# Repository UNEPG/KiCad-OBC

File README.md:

# KiCad-OBC
UNEPG Course Module 4 Lecture 2: PCB Design with KiCad Course Materials.

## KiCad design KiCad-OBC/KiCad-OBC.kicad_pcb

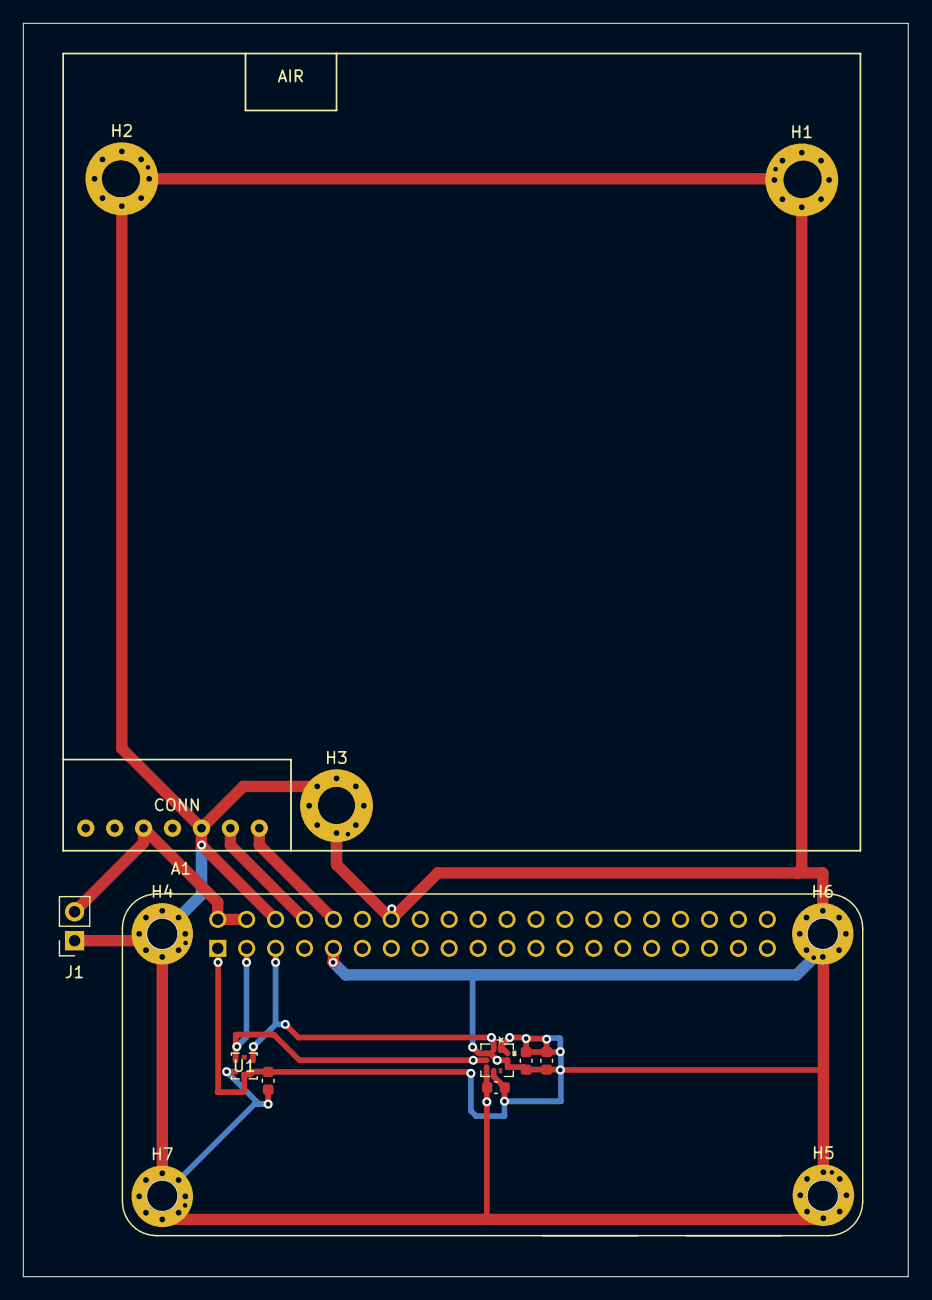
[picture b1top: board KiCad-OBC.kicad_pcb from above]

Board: 2 copper layers, 77.7 x 110.0 mm, 16 parts (0 on the bottom side), 7 nets.

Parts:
A1: ADA3708; RPI-ZERO
C1, C2, C3: 100n; C_0603_1608Metric
C4: 10n; C_0603_1608Metric
H1, H2, H3: 3.2; MountingHole_3.2mm_M3_Pad_Via
H4, H5, H6, H7: 2.75; MountingHole_2.7mm_M2.5_Pad_Via
J1: PWR; PinSocket_1x02_P2.54mm_Vertical
U1: HTS221TR
U2: LPS25H
U3: SDS011

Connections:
+3V3: A1.1 (3V3[1]), C1.1, C2.1, C3.1, C4.1, U1.1 (VDD), U1.6 (CS), U2.1 (VDD_IO), U2.6 (CS), U2.10 (VDD)
+5V: A1.2 (5V[1]), A1.4 (5V[2]), J1.2, U3.3 (5V)
GND: A1.6 (GND[8]), A1.9 (GND[1]), A1.14 (GND[4]), C1.2, C2.2, C3.2, C4.2, H1.1, H2.1, H3.1, H4.1, H5.1, H6.1, H7.1, J1.1, U1.5 (GND), U2.3 (RESERVED), U2.5 (SDO/SA0), U2.8 (GND), U2.9 (GND), U3.5 (GND)
RXPi: A1.10 (RXD0/GPIO15), U3.7 (TX)
SCL: A1.5 (GPIO3/SCL), U1.2 (SCL/SPC), U2.2 (SCL/SPC)
SDA: A1.3 (GPIO2/SDA), U1.4 (SDA/SDI/SDO), U2.4 (SDA/SDI/SDO)
TXPi: A1.8 (TXD0/GPIO14), U3.6 (RX)

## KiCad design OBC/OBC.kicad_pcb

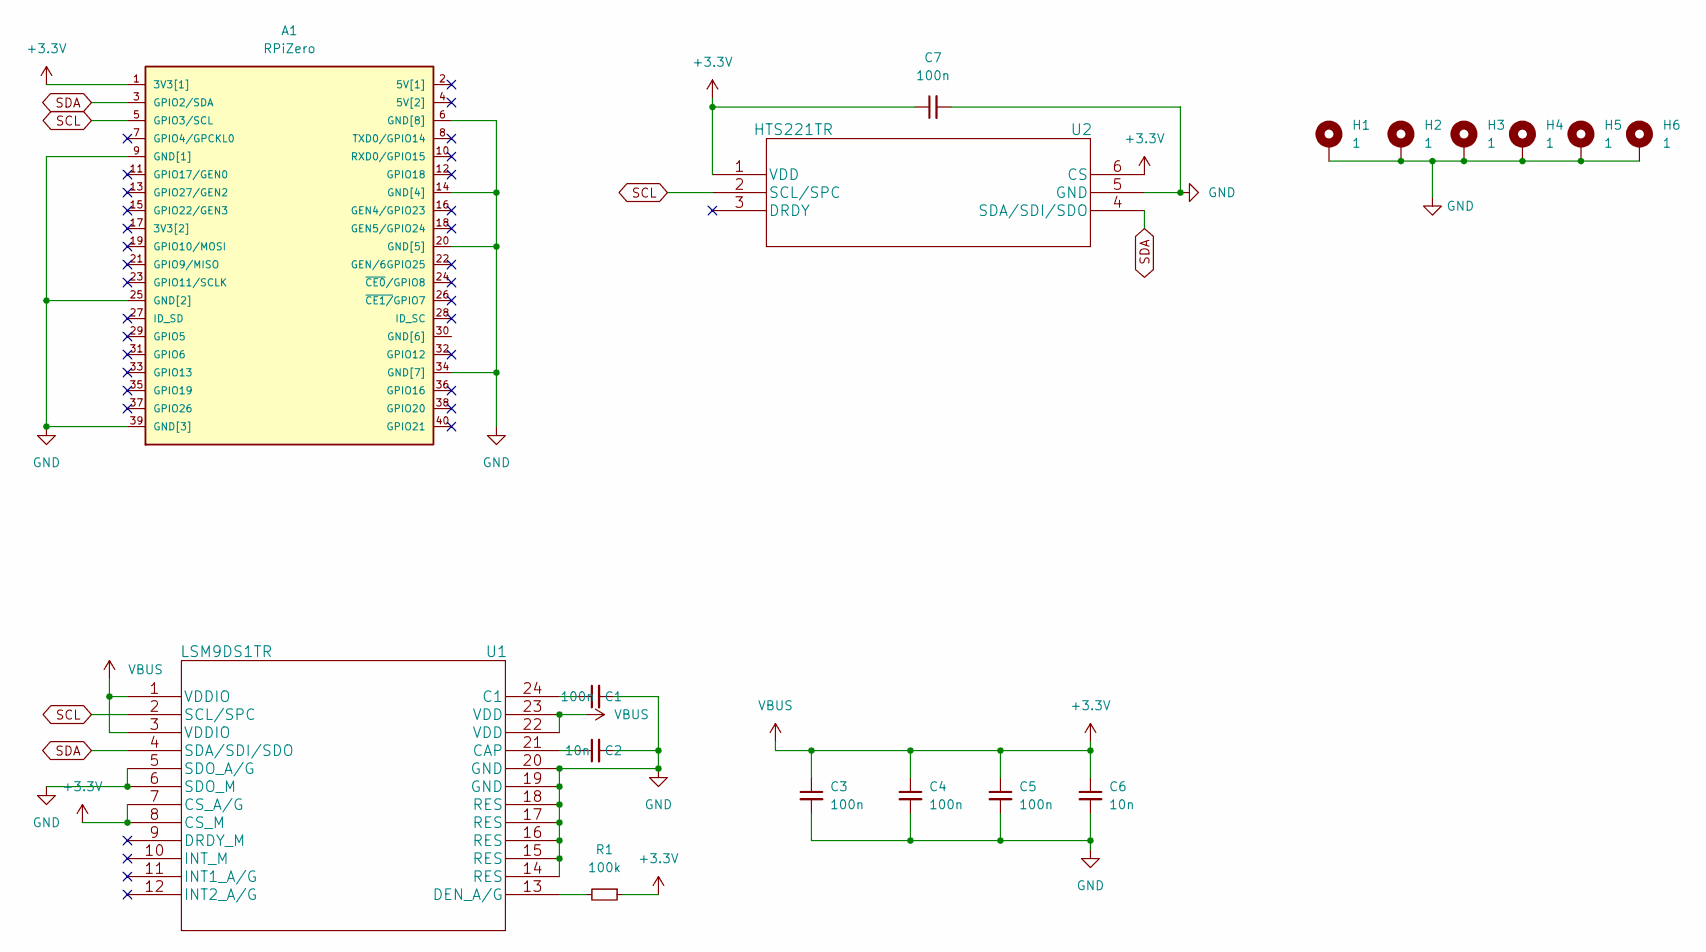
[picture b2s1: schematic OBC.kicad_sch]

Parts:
A1: RPiZero
C1, C3, C4, C5, C7: 100n; C_0201_0603Metric
C2, C6: 10n; C_0201_0603Metric
H1, H2, H3, H4, H5, H6: 1; MountingHole_2.7mm_M2.5_Pad_Via
R1: 100k; R_0201_0603Metric
U1: LSM9DS1TR
U2: HTS221TR

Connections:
+3V3: A1.1 (3V3[1]), C3.1, C4.1, C5.1, C6.1, C7.1, R1.1, U1.1 (VDDIO), U1.3 (VDDIO), U1.7 (CS_A/G), U1.8 (CS_M), U1.22 (VDD), U1.23 (VDD), U2.1 (VDD), U2.6 (CS)
GND: A1.6 (GND[8]), A1.9 (GND[1]), A1.14 (GND[4]), A1.20 (GND[5]), A1.25 (GND[2]), A1.34 (GND[7]), A1.39 (GND[3]), C1.2, C2.2, C3.2, C4.2, C5.2, C6.2, C7.2, H1.1, H2.1, H3.1, H4.1, H5.1, H6.1, U1.5 (SDO_A/G), U1.6 (SDO_M), U1.14 (RES), U1.15 (RES), U1.16 (RES), U1.17 (RES), U1.18 (RES), U1.19 (GND), U1.20 (GND), U2.5 (GND)
unnamed: C1.1, U1.24 (C1)
unnamed: C2.1, U1.21 (CAP)
unnamed: R1.2, U1.13 (DEN_A/G)
SCL: A1.5 (GPIO3/SCL), U1.2 (SCL/SPC), U2.2 (SCL/SPC)
SDA: A1.3 (GPIO2/SDA), U1.4 (SDA/SDI/SDO), U2.4 (SDA/SDI/SDO)

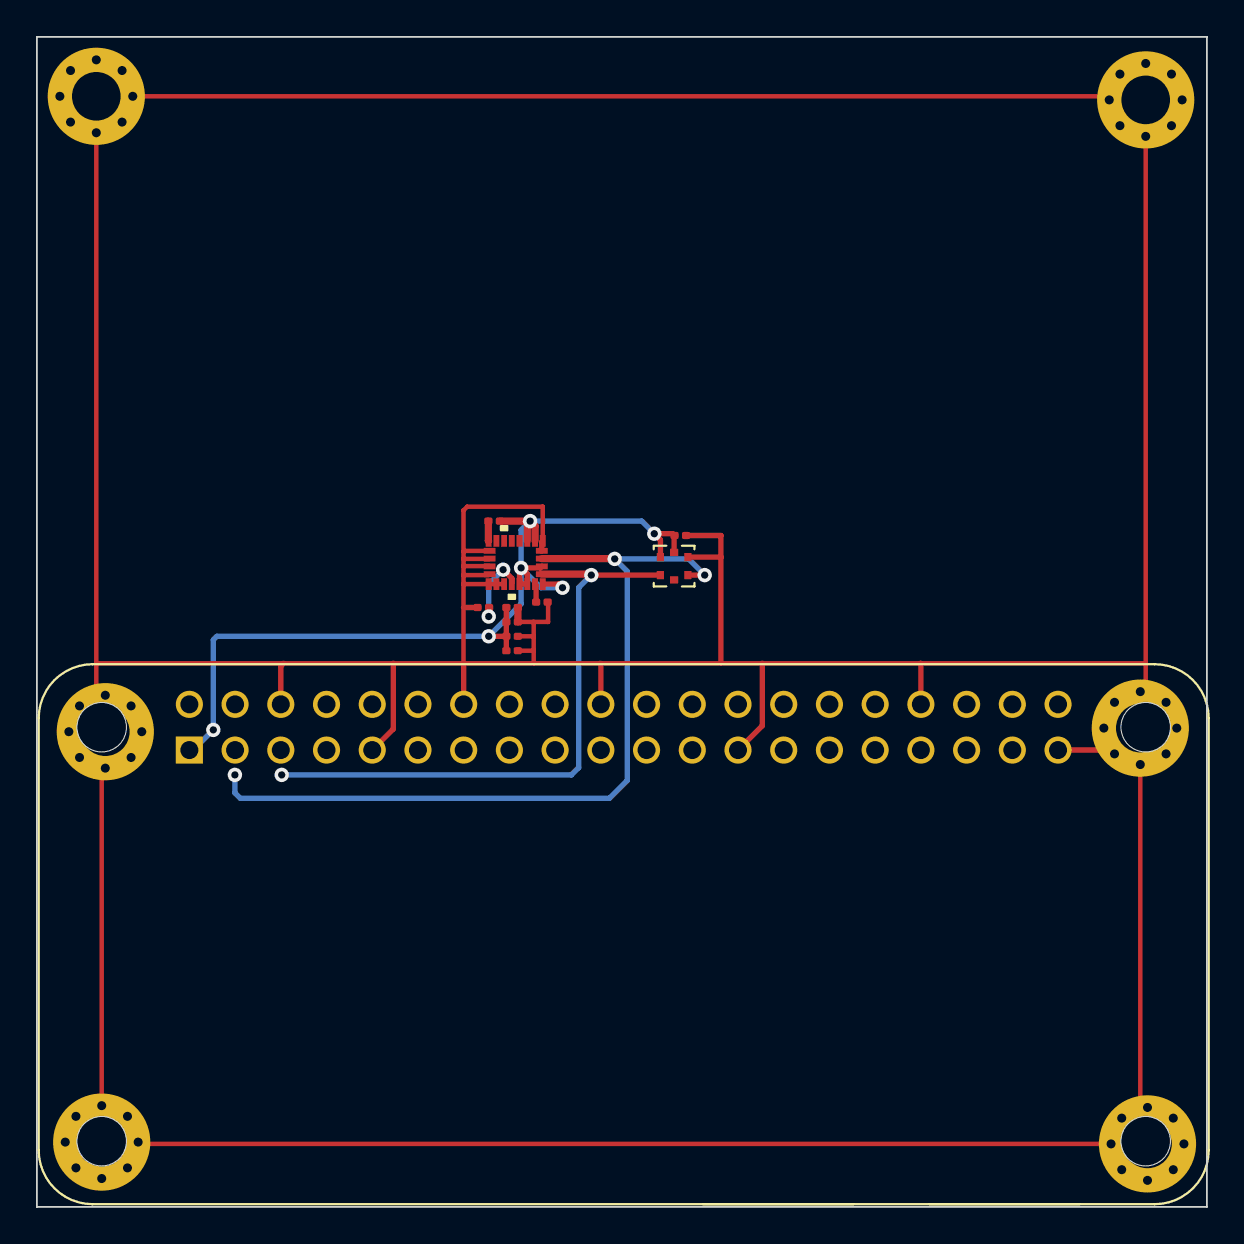
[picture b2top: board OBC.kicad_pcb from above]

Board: 2 copper layers, 65.0 x 65.0 mm, 17 parts (0 on the bottom side), 7 nets.

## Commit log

2022-02-24 updated the libs and footprints as OBC
    ok
2022-02-24 updated foot prints of the sensors
2022-02-24 schematics finished
2022-02-25 start obc again with new place
2022-02-25 schematics done, foot prints assigned
2022-02-25 v0.3-pcb ok
2022-02-25 deleted proj and now only includes datasheets and parts
2022-02-25 updated contents about the sds011
2022-02-26 added the sds011
2022-02-26 added sds011 materials
2022-02-26 symbol library created, footprint library created, new project created
2022-02-26 added all 3ds for foot prints
2022-02-26 pcb done
2022-02-26 updated exported 3d files
2022-02-26 updated images
2022-02-26 using online images to render them correctly
2022-02-28 Added a README-RU.md

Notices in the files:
parts and their libraries:
Copyright 2021 Accelerated Designs. All rights reserved.
